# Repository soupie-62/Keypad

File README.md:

Version 2C:
----------
100mm x 60mm
Small enough for cheaper PCB costs
Problems:
	Mounting holes too close too switches

Version 2B:
----------
49 keys, 120 mm x 55 mm board
Improved button spacing, better mounting hole placement
Problem: Itead Studio want boards <10 cm (100mm)
	Need to move mounting holes, and squeeze buttons together a bit…

Version 2A:
----------
44 keys, 10cm x 5cm board
Improved button spacing, better mounting hole placement

Version 1:
----------
49 keys, 10cm x 5cm board

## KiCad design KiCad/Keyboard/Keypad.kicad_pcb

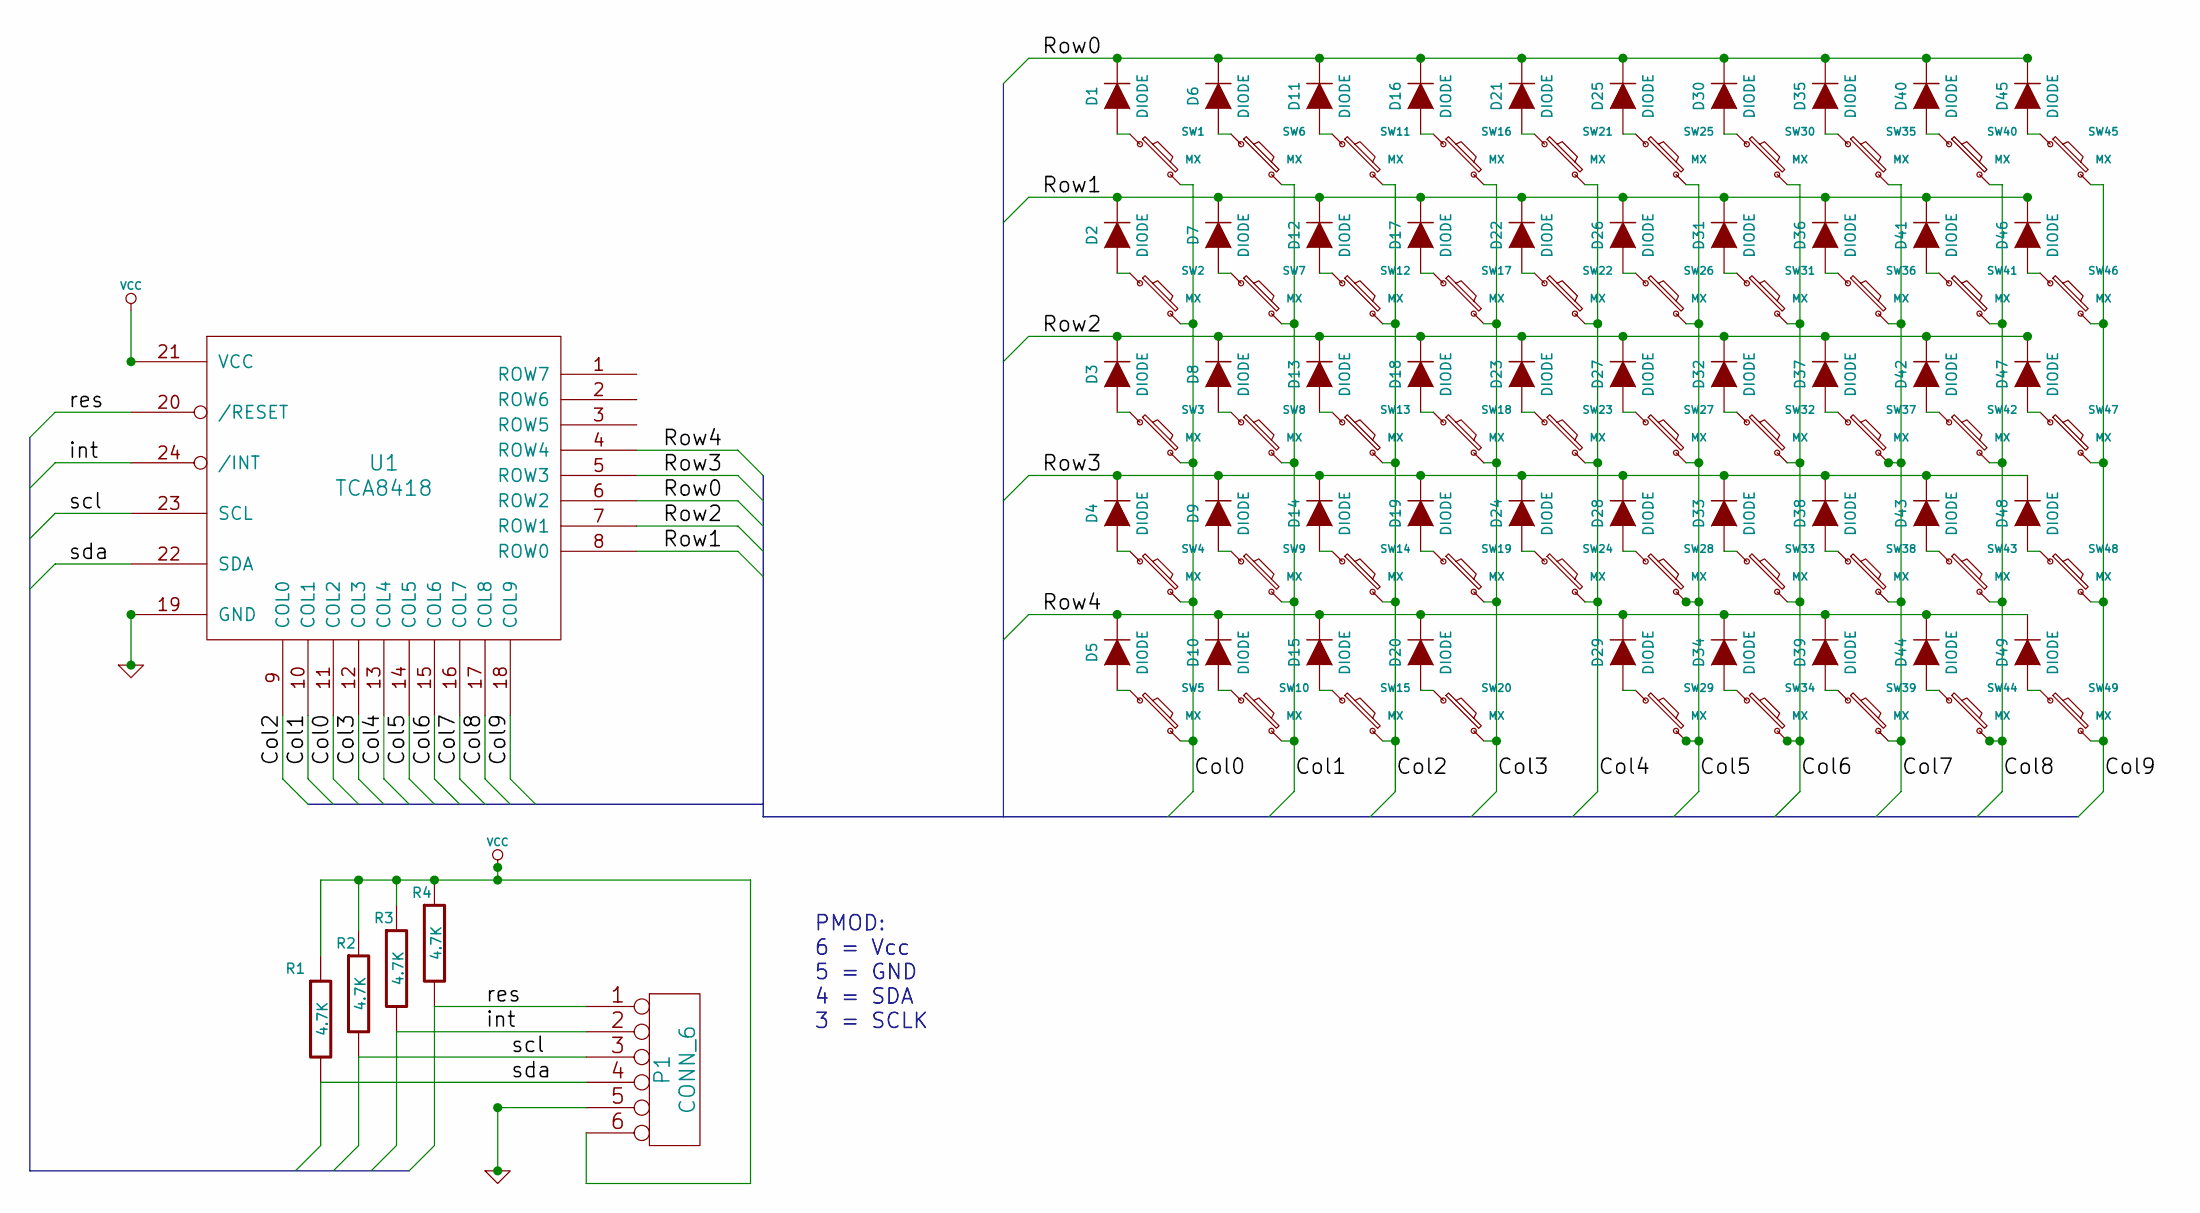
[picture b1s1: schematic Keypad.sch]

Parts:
D1, D2, D3, D4, D5, D6, D7, D8, D9, D10, D11, D12, D13, D14, D15, D16, D17, D18, D19, D20, D21, D22, D23, D24, D25, D26, D27, D28, D29, D30, D31, D32, D33, D34, D35, D36, D37, D38, D39, D40, D41, D42, D43, D44, D45, D46, D47, D48, D49: DIODE
P1: CONN_6
R1, R2, R3, R4: 4.7K
SW1, SW2, SW3, SW4, SW5, SW6, SW7, SW8, SW9, SW10, SW11, SW12, SW13, SW14, SW15, SW16, SW17, SW18, SW19, SW20, SW21, SW22, SW23, SW24, SW25, SW26, SW27, SW28, SW29, SW30, SW31, SW32, SW33, SW34, SW35, SW36, SW37, SW38, SW39, SW40, SW41, SW42, SW43, SW44, SW45, SW46, SW47, SW48, SW49: MX
U1: TCA8418

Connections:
/Col0: SW1.2, SW2.2, SW3.2, SW4.2, SW5.2, U1.11 (COL2)
/Col1: SW6.2, SW7.2, SW8.2, SW9.2, SW10.2, U1.10 (COL1)
/Col2: SW11.2, SW12.2, SW13.2, SW14.2, SW15.2, U1.9 (COL0)
/Col3: SW16.2, SW17.2, SW18.2, SW19.2, SW20.2, U1.12 (COL3)
/Col4: SW21.2, SW22.2, SW23.2, SW24.2, U1.13 (COL4)
/Col5: SW25.2, SW26.2, SW27.2, SW28.2, SW29.2, U1.14 (COL5)
/Col6: SW30.2, SW31.2, SW32.2, SW33.2, SW34.2, U1.15 (COL6)
/Col7: SW35.2, SW36.2, SW37.2, SW38.2, SW39.2, U1.16 (COL7)
/Col8: SW40.2, SW41.2, SW42.2, SW43.2, SW44.2, U1.17 (COL8)
/Col9: SW45.2, SW46.2, SW47.2, SW48.2, SW49.2, U1.18 (COL9)
/Row0: D1.2 (K), D6.2 (K), D11.2 (K), D16.2 (K), D21.2 (K), D25.2 (K), D30.2 (K), D35.2 (K), D40.2 (K), D45.2 (K), U1.6 (ROW2)
/Row1: D2.2 (K), D7.2 (K), D12.2 (K), D17.2 (K), D22.2 (K), D26.2 (K), D31.2 (K), D36.2 (K), D41.2 (K), D46.2 (K), U1.8 (ROW0)
/Row2: D3.2 (K), D8.2 (K), D13.2 (K), D18.2 (K), D23.2 (K), D27.2 (K), D32.2 (K), D37.2 (K), D42.2 (K), D47.2 (K), U1.7 (ROW1)
/Row3: D4.2 (K), D9.2 (K), D14.2 (K), D19.2 (K), D24.2 (K), D28.2 (K), D33.2 (K), D38.2 (K), D43.2 (K), D48.2 (K), U1.5 (ROW3)
/Row4: D5.2 (K), D10.2 (K), D15.2 (K), D20.2 (K), D29.2 (K), D34.2 (K), D39.2 (K), D44.2 (K), D49.2 (K), U1.4 (ROW4)
/int: P1.2, R3.2, U1.24 (/INT)
/res: P1.1, R4.2, U1.20 (/RESET)
/scl: P1.3, R2.2, U1.23 (SCL)
/sda: P1.4, R1.2, U1.22 (SDA)
GND: P1.5, U1.19 (GND)
unnamed: D43.1 (A), SW43.1
unnamed: D42.1 (A), SW42.1
unnamed: D45.1 (A), SW45.1
unnamed: D39.1 (A), SW39.1
unnamed: D40.1 (A), SW40.1
unnamed: D41.1 (A), SW41.1
unnamed: D44.1 (A), SW44.1
unnamed: D49.1 (A), SW49.1
unnamed: D46.1 (A), SW46.1
unnamed: D47.1 (A), SW47.1
unnamed: D48.1 (A), SW48.1
unnamed: D31.1 (A), SW31.1
unnamed: D32.1 (A), SW32.1
unnamed: D33.1 (A), SW33.1
unnamed: D35.1 (A), SW35.1
unnamed: D24.1 (A), SW24.1
unnamed: D28.1 (A), SW28.1
unnamed: D29.1 (A), SW29.1
unnamed: D30.1 (A), SW30.1
unnamed: D38.1 (A), SW38.1
unnamed: D34.1 (A), SW34.1
unnamed: D37.1 (A), SW37.1
unnamed: D36.1 (A), SW36.1
unnamed: D2.1 (A), SW2.1
unnamed: D3.1 (A), SW3.1
unnamed: D4.1 (A), SW4.1
unnamed: D1.1 (A), SW1.1
unnamed: D20.1 (A), SW20.1
unnamed: D19.1 (A), SW19.1
unnamed: D21.1 (A), SW21.1
unnamed: D22.1 (A), SW22.1
unnamed: D18.1 (A), SW18.1
unnamed: D15.1 (A), SW15.1
unnamed: D25.1 (A), SW25.1
unnamed: D26.1 (A), SW26.1
unnamed: D27.1 (A), SW27.1
unnamed: D23.1 (A), SW23.1
unnamed: D9.1 (A), SW9.1
unnamed: D5.1 (A), SW5.1
unnamed: D10.1 (A), SW10.1
unnamed: D11.1 (A), SW11.1
unnamed: D7.1 (A), SW7.1
unnamed: D6.1 (A), SW6.1
unnamed: D8.1 (A), SW8.1
unnamed: D14.1 (A), SW14.1
unnamed: D16.1 (A), SW16.1
unnamed: D17.1 (A), SW17.1
unnamed: D13.1 (A), SW13.1
unnamed: D12.1 (A), SW12.1
VCC: P1.6, R1.1, R2.1, R3.1, R4.1, U1.21 (VCC)

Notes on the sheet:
PMOD: 6 = Vcc 5 = GND 4 = SDA 3 = SCLK

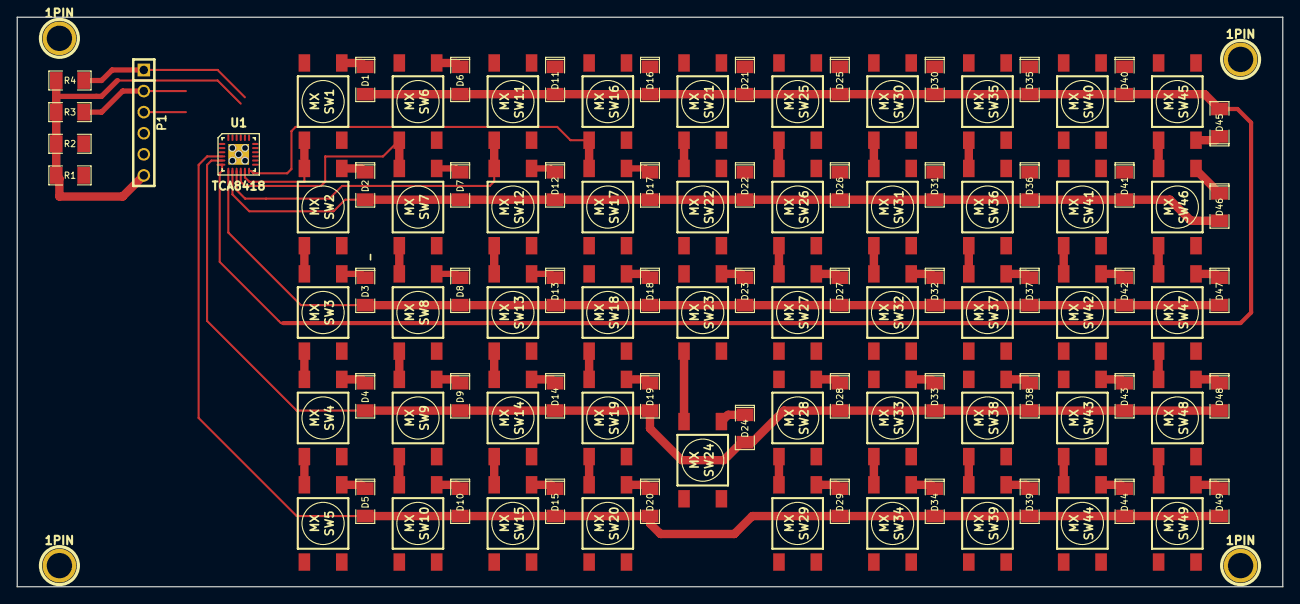
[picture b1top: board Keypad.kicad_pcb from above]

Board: 2 copper layers, 152.4 x 68.6 mm, 108 parts (0 on the bottom side), 70 nets.

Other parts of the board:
1PIN, 1PIN#2, 1PIN#3, 1PIN#4: P***; 1pin

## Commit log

2013-10-04 First time user
2013-10-04 Version 0.1 initial files
2013-10-25 Update for 10cm x 5cm PCB
2013-10-25 Adding extra files
2014-01-30 updating files
2014-01-30 Update 2C: Jan 2014
2014-02-02 2c.1
    Adding picture to readme.md
2014-02-02 Commiting again
2015-08-16 Update 2c
    2 layouts, and a virtual keypad for use with Android Nexus 7
2015-08-18 Tidy up structure
2015-08-18 Tidy up
